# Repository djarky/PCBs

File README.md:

# PCBs
Various PCBs

- game controller based on digispark
- clap switch with relay
- amps?
- others

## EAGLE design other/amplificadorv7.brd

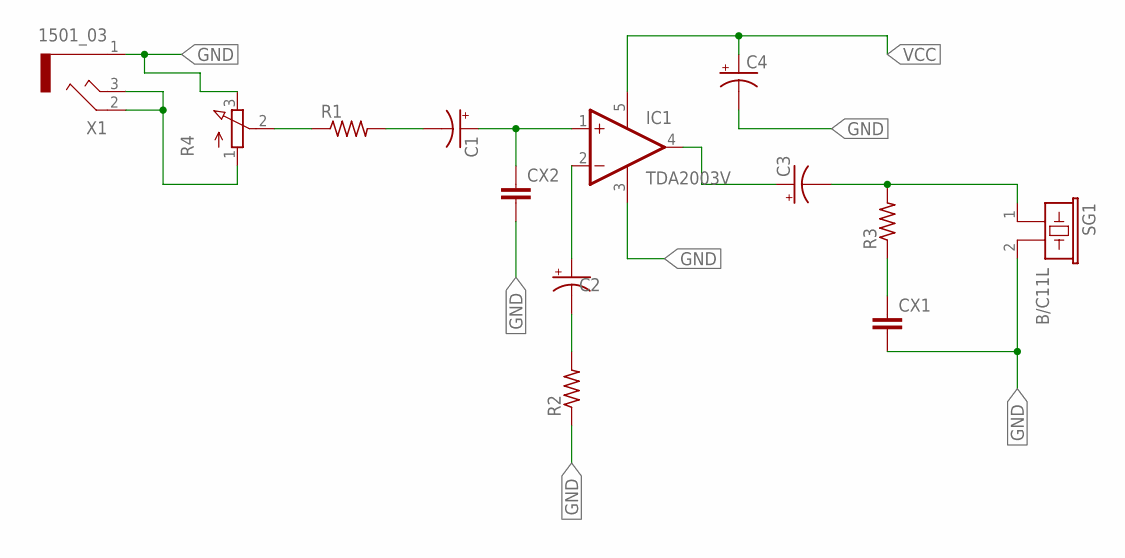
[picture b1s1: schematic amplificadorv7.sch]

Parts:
C1, C2, C3, C4: CPOL-USB45181B; B45181B
CX1, CX2: CXXC10B6; XC10B6
IC1: TDA2003V; CB360
R1, R2, R3: R-US_0204/7; 0204/7
R4: 3RP/1610N
SG1: B/C11L
X1: 1501_03

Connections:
GND: C4.-, CX1.2, CX2.2, IC1.3 (GND), R2.1, R4.3 (E), SG1.2, X1.1
unnamed: C1.-, R1.2
unnamed: C1.+, CX2.1, IC1.1 (+IN)
unnamed: C2.+, IC1.2 (-IN)
unnamed: C2.-, R2.2
unnamed: R1.1, R4.2 (S)
unnamed: C3.+, IC1.4 (OUT)
unnamed: C3.-, R3.2, SG1.1
unnamed: CX1.1, R3.1
unnamed: R4.1 (A), X1.2, X1.3
VCC: C4.+, IC1.5 (V+)

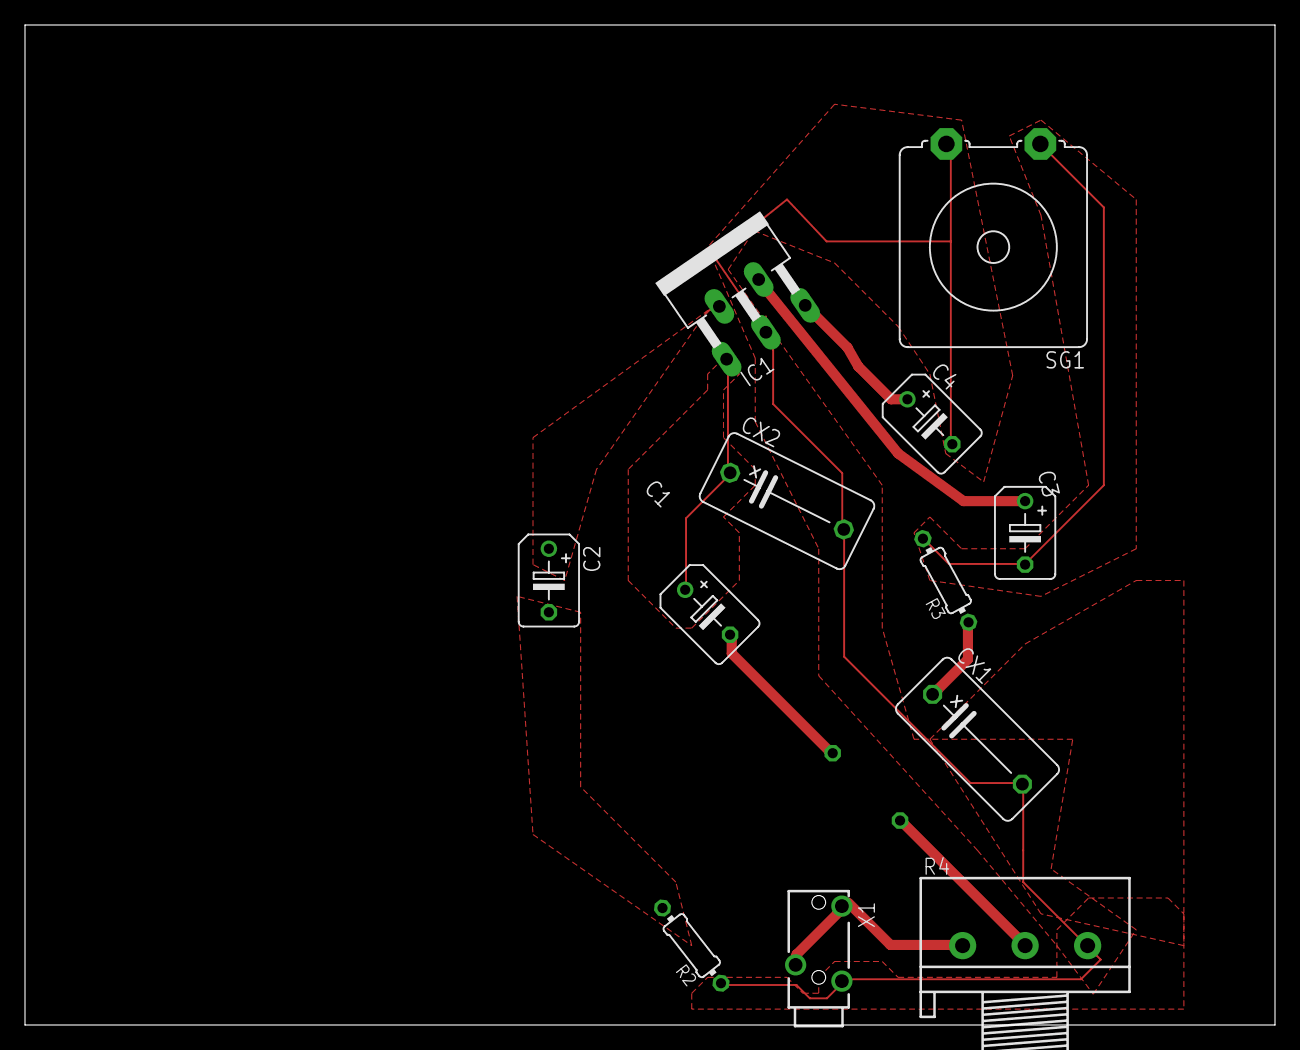
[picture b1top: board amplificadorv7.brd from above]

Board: 2 copper layers, 100.0 x 80.0 mm, 13 parts (1 on the bottom side), 11 nets.

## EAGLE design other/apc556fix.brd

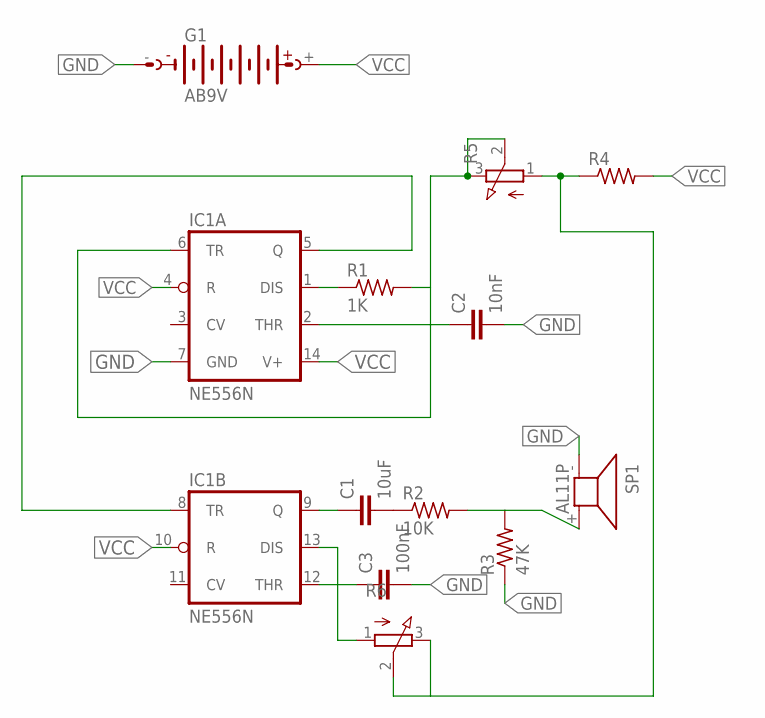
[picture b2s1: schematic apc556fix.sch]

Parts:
C1: 10uF; C025-030X050
C2: 10nF; C025-030X050
C3: 100nF; C025-030X050
G1: AB9V
IC1: NE556N; DIL14
R1: 1K; 0204/5
R2: 10K; 0204/7
R3: 47K; 0204/7
R4: R-US_0204/7; 0204/7
R5, R6: 3RP/1610N
SP1: AL11P

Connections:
GND: C2.2, C3.2, G1.-, IC1.7 (GND), R3.1, SP1.- (1)
unnamed: IC1.5 (Q), IC1.8 (TR)
unnamed: C2.1, IC1.2 (THR), IC1.6 (TR), R1.2, R5.2 (S), R5.3 (E)
unnamed: IC1.1 (DIS), R1.1
unnamed: C1.1, IC1.9 (Q)
unnamed: C1.2, R2.1
unnamed: R2.2, R3.2, SP1.+ (2)
unnamed: C3.1, IC1.12 (THR), IC1.13 (DIS), R6.1 (A)
unnamed: R4.1, R5.1 (A), R6.2 (S), R6.3 (E)
VCC: G1.+, IC1.4 (R), IC1.10 (R), IC1.14 (V+), R4.2

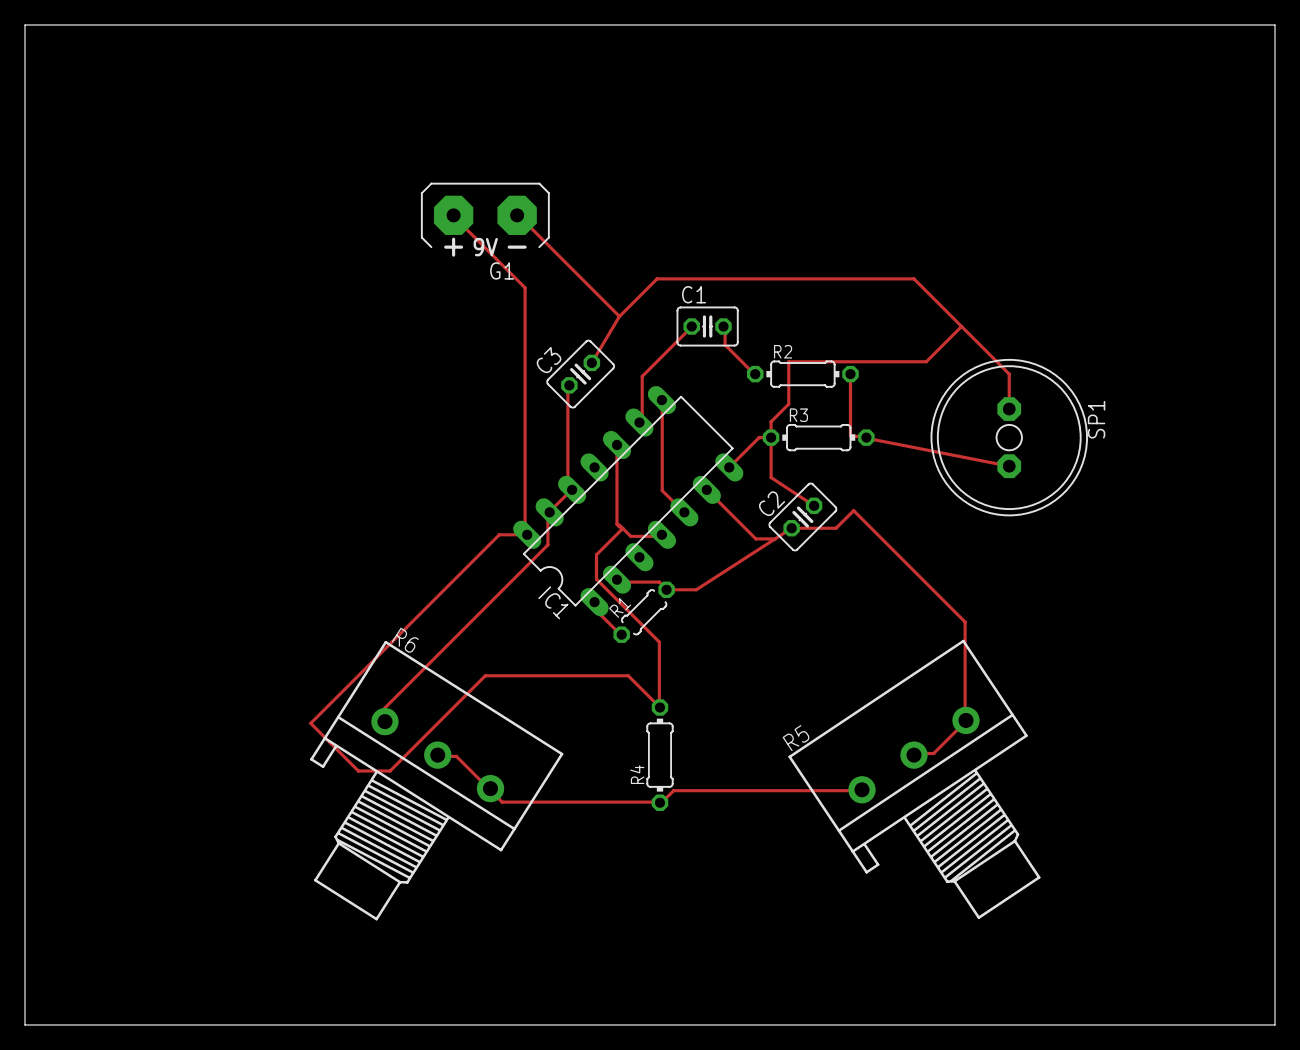
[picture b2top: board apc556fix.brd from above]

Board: 2 copper layers, 100.0 x 80.0 mm, 12 parts (0 on the bottom side), 10 nets.

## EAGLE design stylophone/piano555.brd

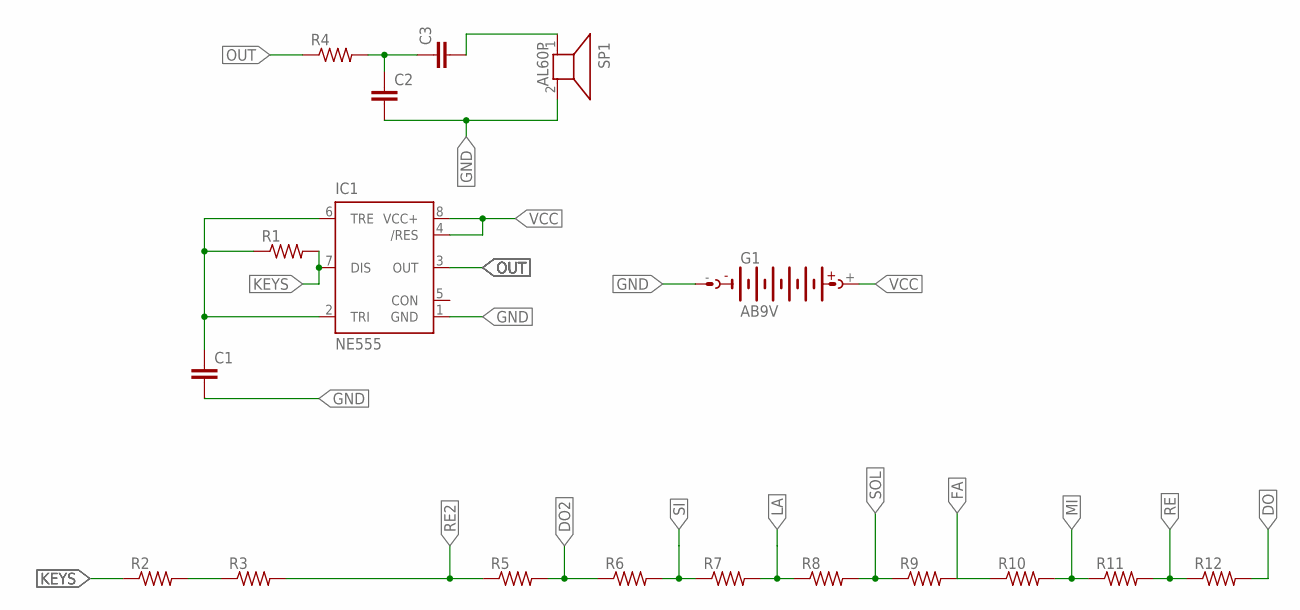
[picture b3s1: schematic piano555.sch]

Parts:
C1, C2, C3: C-EU025-030X050; C025-030X050
G1: AB9V
IC1: NE555; DIL-08
R1, R2, R3, R4, R5, R6, R7, R8, R9, R10, R11, R12: R-US_0204/7; 0204/7
SP1: AL60P

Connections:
DO: R12.2
DO2: R5.2, R6.1
FA: R9.2, R10.1
GND: C1.2, C2.2, G1.-, IC1.1 (GND), SP1.2
KEYS: IC1.7 (DIS), R1.2, R2.1
LA: R7.2, R8.1
MI: R10.2, R11.1
unnamed: C1.1, IC1.2 (TRI), IC1.6 (TRE), R1.1
unnamed: R2.2, R3.1
unnamed: C2.1, C3.1, R4.2
unnamed: C3.2, SP1.1
OUT: IC1.3 (OUT), R4.1
RE: R11.2, R12.1
RE2: R3.2, R5.1
SI: R6.2, R7.1
SOL: R8.2, R9.1
VCC: G1.+, IC1.4 (/RES), IC1.8 (VCC+)

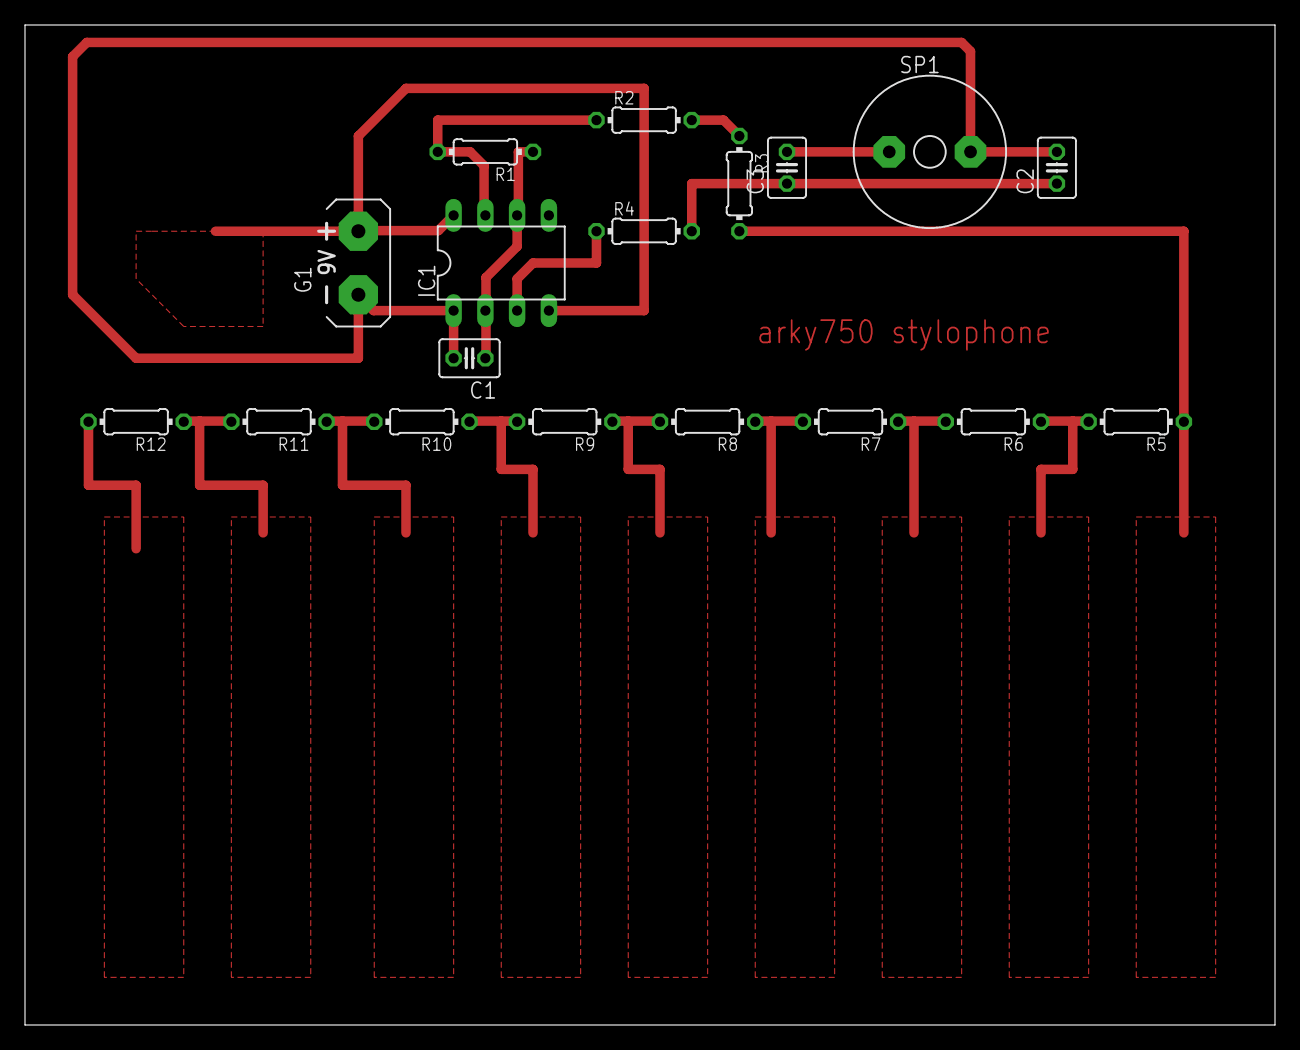
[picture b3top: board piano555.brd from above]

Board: 2 copper layers, 100.0 x 80.0 mm, 18 parts (0 on the bottom side), 16 nets.

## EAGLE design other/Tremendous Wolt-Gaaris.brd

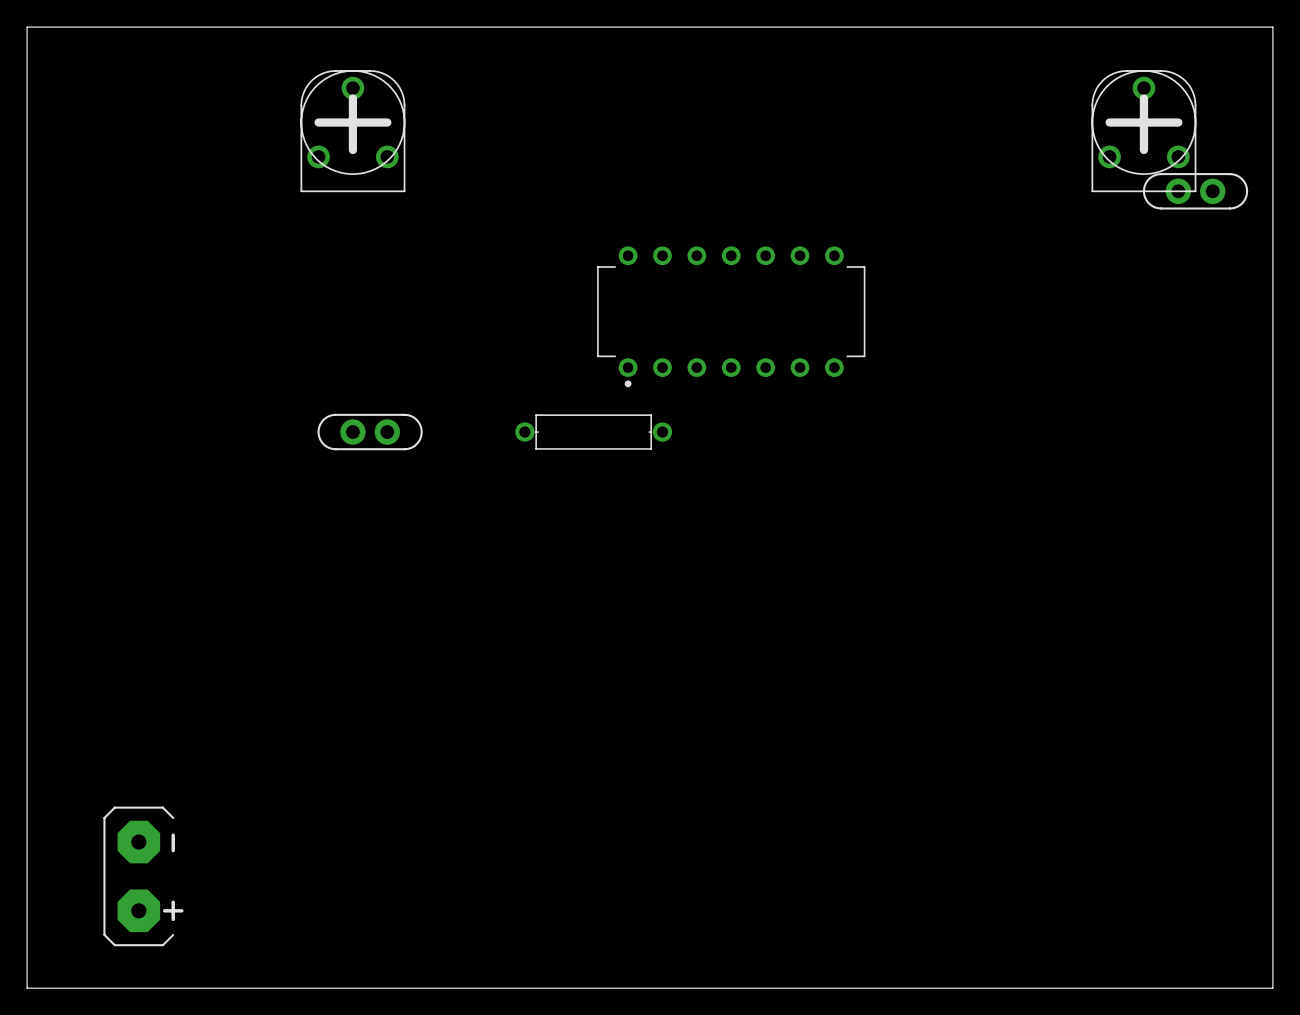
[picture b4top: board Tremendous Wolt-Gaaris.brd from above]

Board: 2 copper layers, 92.0 x 71.0 mm, 7 parts (0 on the bottom side), 6 nets, no tracks yet.

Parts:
BAT1: 9V; BATTERY-GENERIC
C1: 100n; CAP-THRU-2.54MM
C2: 10n; CAP-THRU-2.54MM
R2: 1k; RESAD1016W63L850D250B
RPOT1, RPOT2: 470k; HA-06-SM065
U1: NA556_DIP; DIP826W53P254L1930H508Q14B

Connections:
BAT1+: BAT1.+, RPOT1.1, RPOT1.2, RPOT2.1, RPOT2.2, U1.4, U1.10, U1.14
BAT1-: BAT1.-, C1.2, C2.1, U1.7
U1_DIS1: R2.2, RPOT1.3, U1.1
U1_DIS2: C1.1, RPOT2.3, U1.12, U1.13
U1_THR1: C2.2, R2.1, U1.2, U1.6
U1_TR2: U1.5, U1.8

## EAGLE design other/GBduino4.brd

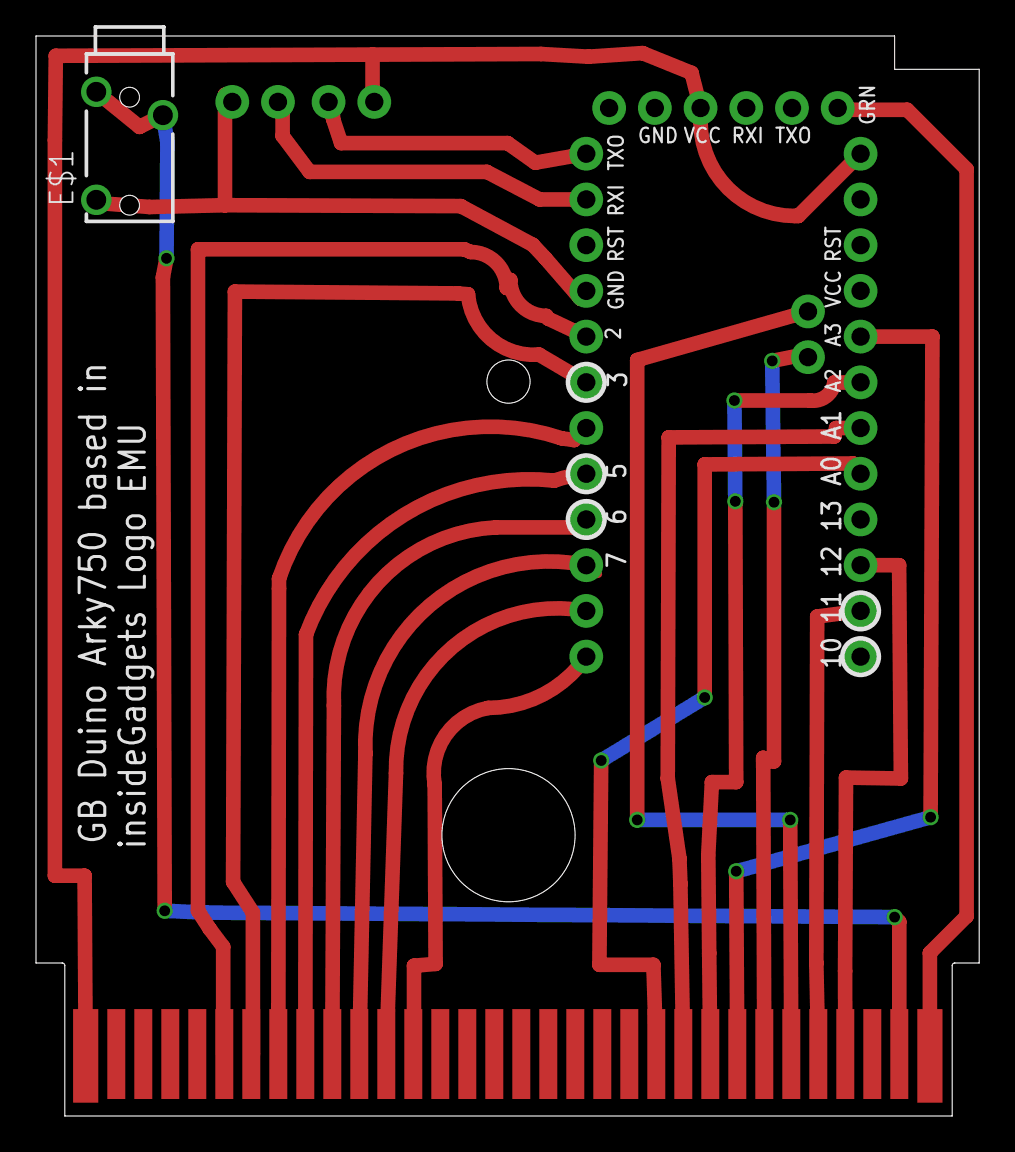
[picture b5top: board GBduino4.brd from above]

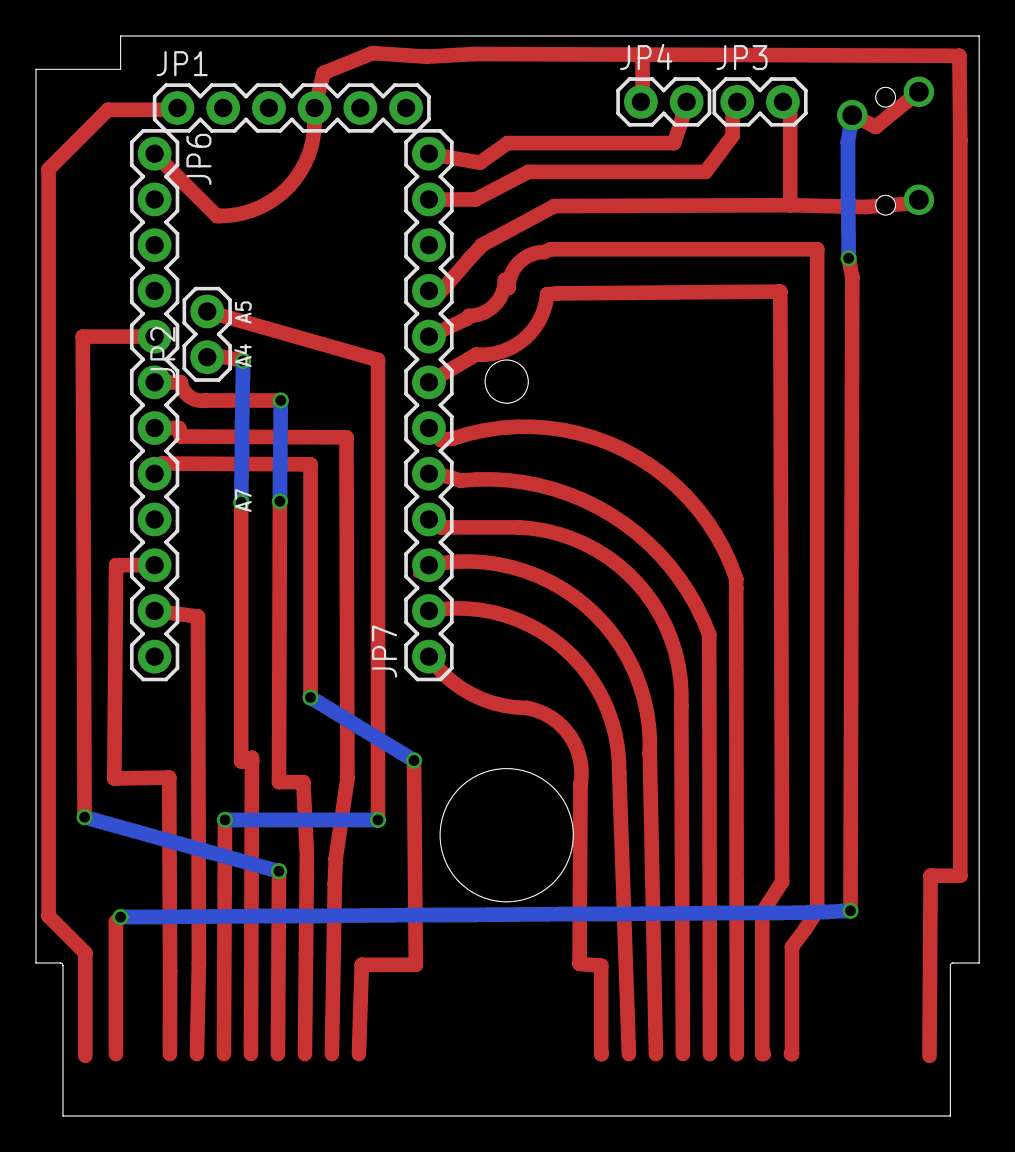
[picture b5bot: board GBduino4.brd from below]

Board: 2 copper layers, 52.4 x 60.0 mm, 8 parts (6 on the bottom side), 20 nets.

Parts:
E$1: 1501_03
JP1: FTDI Basic; 1X06
JP2, JP3, JP4: 1X02
JP6, JP7: 1X12
U$1: GB_CARTPADS; GB_CART_PADS

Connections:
A0: JP7.8, U$1.6
A1: JP7.7, U$1.7
A2: JP7.6, U$1.8
A3: JP7.5, U$1.9
A7: JP7.1, U$1.13
A18: JP6.8, U$1.22
AUDIO_IN: E$1.1, E$1.2, U$1.31
D1: JP6.7, U$1.23
D4: JP2.1, U$1.26
D5: JP2.2, U$1.27
D6: JP6.11, U$1.28
D7: JP6.10, U$1.29
D8: JP7.2, U$1.12
GND: JP1.1, U$1.32
RAW: JP1.4, JP4.1, JP6.1, U$1.1
S$2: E$1.3, JP3.2, JP7.9
S$6: JP7.4, U$1.10
S$7: JP7.3, U$1.11
S$14: JP3.1, JP7.11
S$19: JP4.2, JP7.12

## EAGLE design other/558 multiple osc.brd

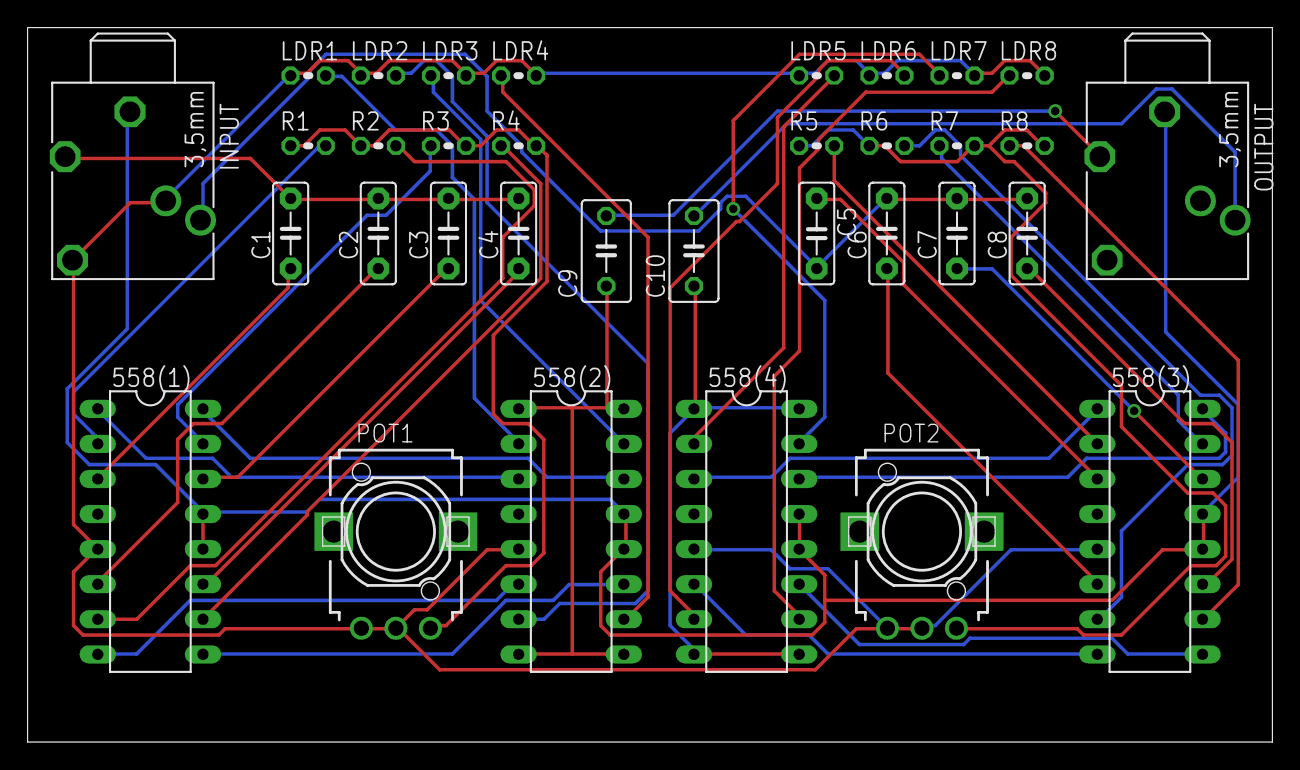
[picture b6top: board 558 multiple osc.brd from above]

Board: 2 copper layers, 90.1 x 51.7 mm, 34 parts (0 on the bottom side), 42 nets.

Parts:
558(1), 558(2), 558(3), 558(4): DIL16
C1, C2, C3, C4, C5, C6, C7, C8: C5B2.5
C9, C10: C050-035X075
INPUT: PG203J
LDR1, LDR2, LDR3, LDR4, LDR5, LDR6, LDR7, LDR8: 0204V
OUTPUT: PG203J
POT1, POT2: 1M; EVUFXM
R1, R2, R3, R4, R5, R6, R7, R8: 0204V

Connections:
GND: 558(1).12, 558(1).13, 558(2).12, 558(2).13, 558(3).12, 558(3).13, 558(4).12, 558(4).13, INPUT.1, OUTPUT.1
INN1: POT1.3, R1.1, R2.1, R3.2, R4.2
INN2: POT2.3, R5.1, R6.1, R7.2, R8.2
INPUT(L): C1.2, C2.2, C3.2, C4.2, INPUT.5
INPUT(R): C5.2, C6.2, C7.2, C8.2, INPUT.2
unnamed: 558(2).2, LDR1.2
unnamed: 558(2).15, LDR3.1
unnamed: 558(2).7, LDR2.2
unnamed: 558(2).10, LDR4.1
unnamed: 558(4).2, LDR5.2
unnamed: 558(4).15, LDR7.1
unnamed: 558(4).7, LDR6.2
unnamed: 558(4).10, LDR8.1
unnamed: C9.2, OUTPUT.5
unnamed: C10.2, OUTPUT.2
OUT1: 558(1).1, 558(2).3
OUT2: 558(3).1, 558(4).3
OUT3: 558(3).16, 558(4).14
OUT4: 558(1).16, 558(2).14
OUT(L): 558(2).1, 558(2).8, 558(2).9, 558(2).16, C9.1
OUT(R): 558(4).1, 558(4).8, 558(4).9, 558(4).16, C10.1
TIM1: 558(1).2, R1.2
TIM2: 558(1).7, R2.2
TIM3: 558(1).10, R4.1
TIM4: 558(1).15, R3.1
TIM5: 558(3).2, R5.2
TIM6: 558(3).7, R6.2
TIM7: 558(3).15, R7.1
TIM8: 558(3).10, R8.1
TR1: 558(1).3, C1.1
TR2: 558(1).6, C2.1
TR3: 558(1).11, C4.1
TR4: 558(1).14, C3.1
TR5: 558(3).3, C5.1
TR6: 558(1).8, 558(2).6
TR7: 558(3).6, C6.1
TR8: 558(1).9, 558(2).11
TR9: 558(3).14, C7.1
TR10: 558(3).11, C8.1
TR11: 558(3).8, 558(4).6
TR12: 558(3).9, 558(4).11
VCC: 558(1).5, 558(2).5, 558(3).5, 558(4).5, INPUT.3, INPUT.4, LDR1.1, LDR2.1, LDR3.2, LDR4.2, LDR5.1, LDR6.1, LDR7.2, LDR8.2, POT1.1, POT1.2, POT2.1, POT2.2

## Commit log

2026-03-16 upgrade cat
